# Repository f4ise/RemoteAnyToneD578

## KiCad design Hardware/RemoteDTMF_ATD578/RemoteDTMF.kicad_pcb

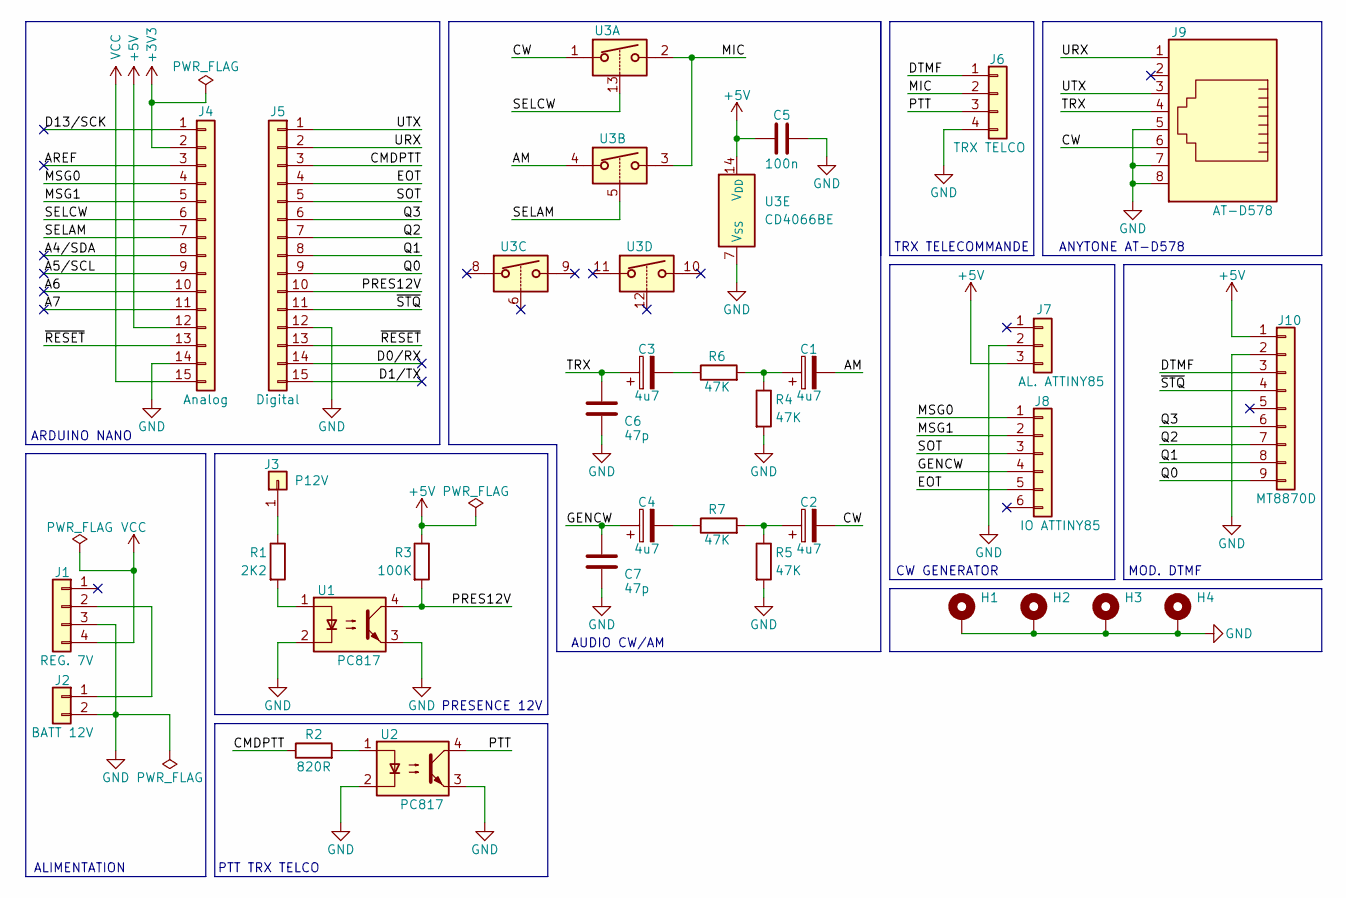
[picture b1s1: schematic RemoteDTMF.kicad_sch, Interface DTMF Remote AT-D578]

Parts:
C1, C2, C3, C4: 4u7; CP_Radial_D5.0mm_P2.50mm
C5: 100n; C_Rect_L7.0mm_W3.5mm_P5.00mm
C6, C7: 47p; C_Rect_L7.0mm_W3.5mm_P5.00mm
H1, H2, H3, H4: MountingHole_Pad; MountingHole_3.2mm_M3_DIN965_Pad
J1: REG. 7V; PinHeader_1x04_P2.54mm_Vertical
J2: BATT 12V; TerminalBlock_MaiXu_MX126-5.0-02P_1x02_P5.00mm
J3: P12V; PinHeader_1x01_P2.54mm_Vertical
J4: Analog; PinHeader_1x15_P2.54mm_Vertical
J5: Digital; PinHeader_1x15_P2.54mm_Vertical
J6: TRX TELCO; PinHeader_1x04_P2.54mm_Vertical
J7: AL. ATTINY85; PinHeader_1x03_P2.54mm_Vertical
J8: IO ATTINY85; PinHeader_1x06_P2.54mm_Vertical
J9: AT-D578; RJ45_Amphenol_54602-x08_Horizontal
J10: MT8870D; PinHeader_1x09_P2.54mm_Vertical
R1: 2K2; R_Axial_DIN0204_L3.6mm_D1.6mm_P7.62mm_Horizontal
R2: 820R; R_Axial_DIN0204_L3.6mm_D1.6mm_P7.62mm_Horizontal
R3: 100K; R_Axial_DIN0204_L3.6mm_D1.6mm_P7.62mm_Horizontal
R4, R5, R6, R7: 47K; R_Axial_DIN0204_L3.6mm_D1.6mm_P7.62mm_Horizontal
U1, U2: PC817; DIP-4_W7.62mm
U3: CD4066BE; DIP-14_W7.62mm

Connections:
+3V3: J4.2
+5V: C5.1, J4.12, J7.3, J10.1, R3.1, U3.14 (V_{DD})
/A4/SDA: J4.8
/A5/SCL: J4.9
/A6: J4.10
/A7: J4.11
/AM: C1.2, U3.4
/AREF: J4.3
/CMDPTT: J5.3, R2.1
/CW: C2.2, J9.6, U3.1
/D0/RX: J5.14
/D1/TX: J5.15
/D13/SCK: J4.1
/DTMF: J6.1, J10.3
/EOT: J5.4, J8.5
/GENCW: C4.1, C7.1, J8.4
/MIC: J6.2, U3.2, U3.3
/MSG0: J4.4, J8.1
/MSG1: J4.5, J8.2
/PRES12V: J5.10, R3.2, U1.4
/PTT: J6.3, U2.4
/Q0: J5.9, J10.9
/Q1: J5.8, J10.8
/Q2: J5.7, J10.7
/Q3: J5.6, J10.6
/SELAM: J4.7, U3.5
/SELCW: J4.6, U3.13
/SOT: J5.5, J8.3
/TRX: C3.1, C6.1, J9.4
/URX: J5.2, J9.1
/UTX: J5.1, J9.3
/~RESET: J4.13, J5.13
/~STQ: J5.11, J10.4
GND: C5.2, C6.2, C7.2, H1.1, H2.1, H3.1, H4.1, J1.3, J2.2, J4.14, J5.12, J6.4, J7.2, J9.5, J9.7, J9.8, J10.2, R4.2, R5.2, U1.2, U1.3, U2.2, U2.3, U3.7 (V_{SS})
unnamed: C1.1, R4.1, R6.2
unnamed: C2.1, R5.1, R7.2
unnamed: C3.2, R6.1
unnamed: C4.2, R7.1
unnamed: J1.2, J2.1
unnamed: J3.1, R1.1
unnamed: R1.2, U1.1
unnamed: R2.2, U2.1
VCC: J1.4, J4.15

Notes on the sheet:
ALIMENTATION
ARDUINO NANO
AUDIO CW/AM
ANYTONE AT-D578
TRX TELECOMMANDE
MOD. DTMF
PRESENCE 12V
PTT TRX TELCO
CW GENERATOR

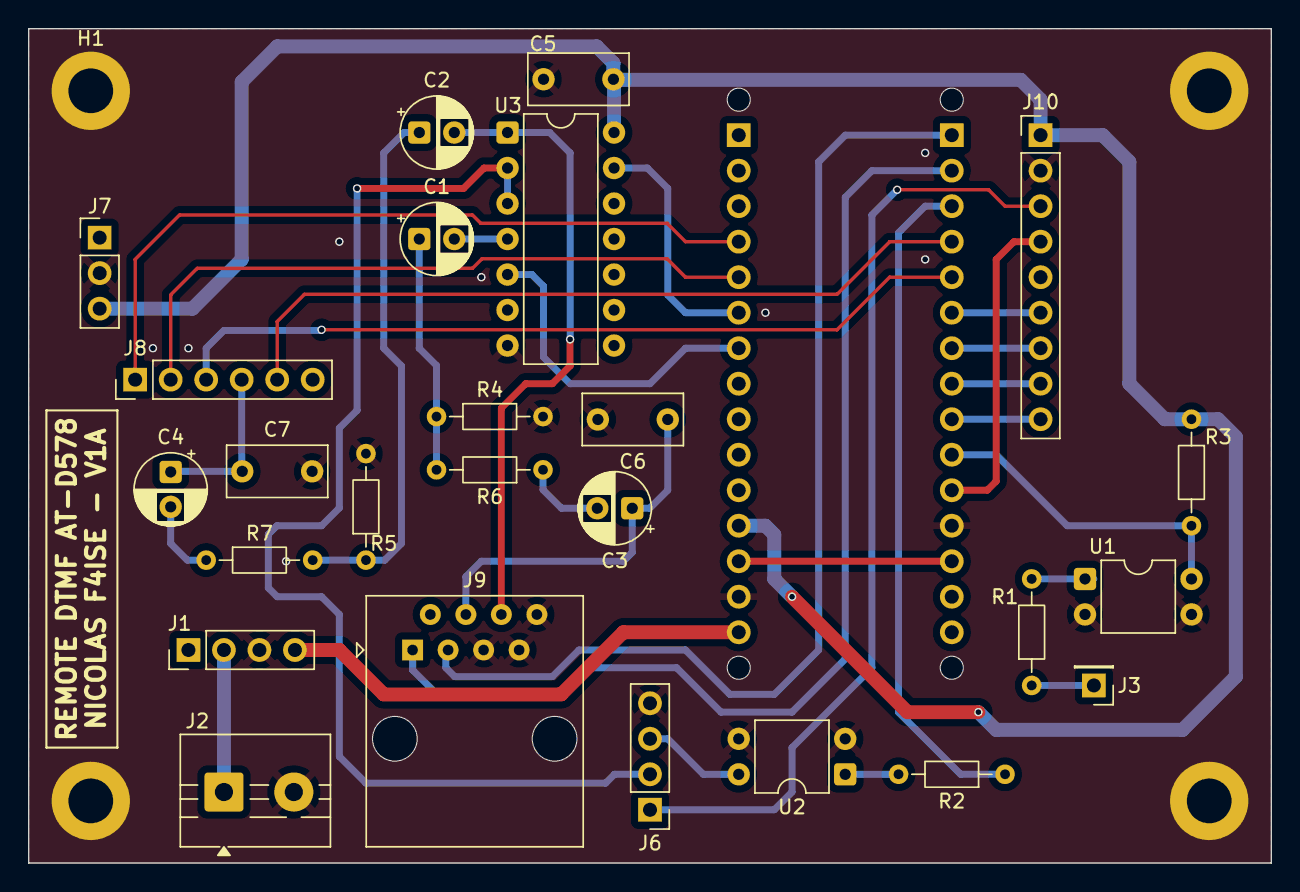
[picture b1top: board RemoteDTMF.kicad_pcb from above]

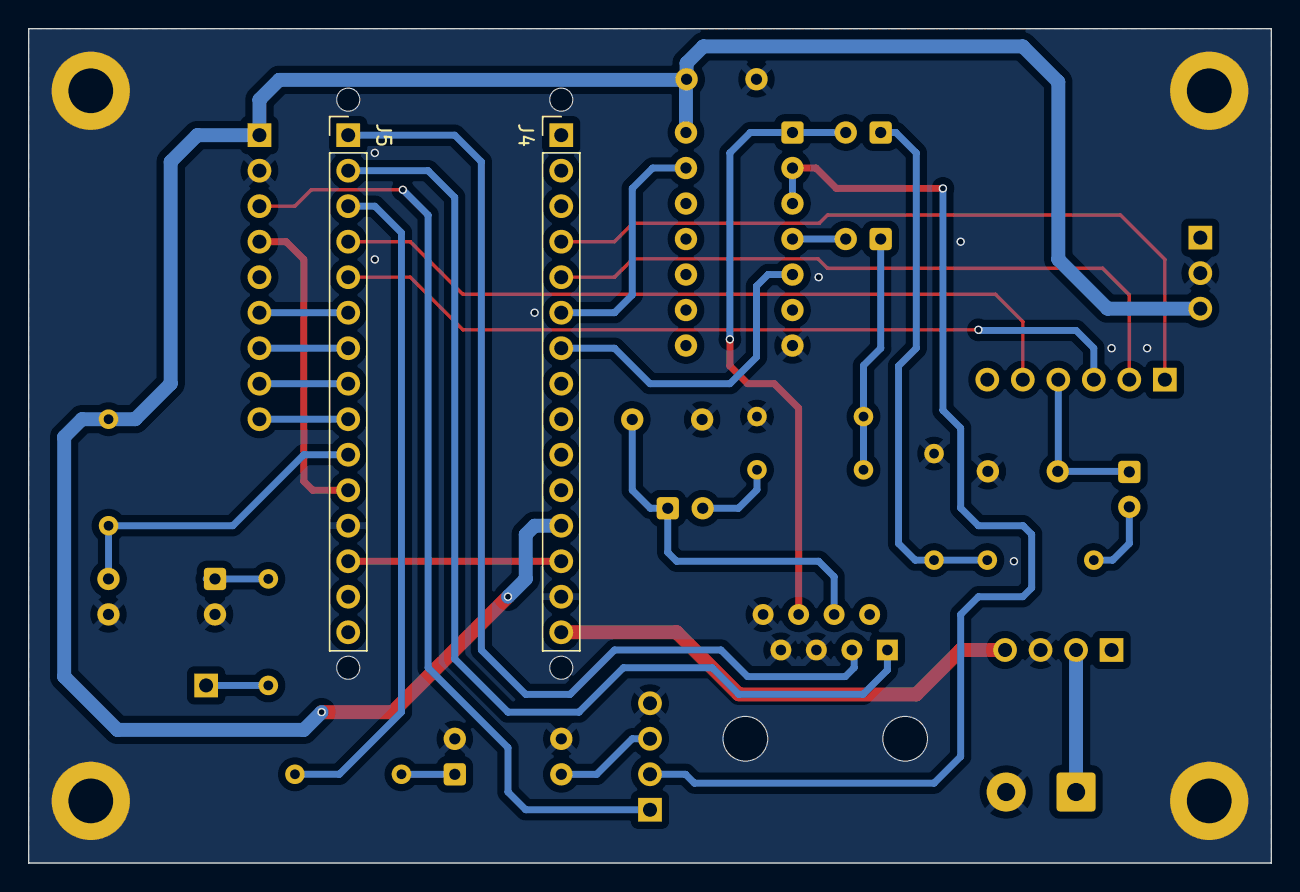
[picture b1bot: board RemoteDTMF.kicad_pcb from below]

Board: 2 copper layers, 88.9 x 59.7 mm, 35 parts (2 on the bottom side), 34 nets.

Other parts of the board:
MH1, MH2, MH3, MH4: MountingHole_65mil

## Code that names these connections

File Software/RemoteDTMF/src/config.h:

#ifndef CONFIG_H
#define CONFIG_H

#define VERSION     "0.9A"

#define LED         LED_BUILTIN

#define dbgSpeed    115200

// UART D578
#define swTX        11
#define swRX        12
#define swSPEED     115200 

// MT8870
#define STQ         2
#define Q0          4
#define Q1          5
#define Q2          6
#define Q3          7
#define timeOutDTMF 10      // Timeout DTMF

// DS3231
#define intRTC      3

// BEACON
#define MSG0_CW     14
#define MSG1_CW     15
#define SOT_CW      8
#define EOT_CW      9

// AUDIO AM
#define DURATION_AM 15      // Send Audio AM X sec.

// OPTO
#define PRES12V1     3      // TBD IO
#define PRES12V2     3      // TBD IO
#define CMDPTT      10

// SWITCH ANA
#define SW_CW       16
#define SW_AM       17

// Logs
#define INF   0
#define WAR   1
#define ERR   2

#endif

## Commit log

2025-09-06 Proof Of Concept
2025-09-06 Update Proof Of Concept
2025-09-07 Manage Press short, Press Long for A, B, C and D touch
2025-09-09 Work In Progress: Add morse beacon
2025-09-12 Update version 0.3A
    - Support Beacon CW
    - Refactoring code main
2025-09-15 Add Beacon CW
2025-09-25 Update Code, Add schematic, Add Docs
2025-09-25 Update schematic, add PCB and Gerber
2025-09-26 Comment Schematic, add PDF
2025-09-26 Update Gerber
2025-09-30 Update to 0.5A
    - Add terminal
    - Add EEPROM
    - add RTC Clock DS3231
2025-09-30 WIP 0.6A & Schematic
    - Support D578 microphone ACK
    - Update schematic
2025-10-04 WIP Update PCB
2025-10-05 WIP Update PCB 2
2025-10-05 WIP Update PCB 3
2025-10-07 WIP Update PCB 4
2025-10-07 Update 0.6A
    - Add relays
    - Add PIO
2025-10-08 Update to 0.7A
    - Change DTMF command
    - Bug fix ACK UART D578
2025-10-08 Update to 0.8A
    - Add Start / Stop mode
    - Add config date and time RTC
2025-10-18 Update 0.9A + Hardware Mega
    - Add EXT BME280
    - Update Doc
    - Add Schematic Remote_Mega
2025-10-30 Update projet
    - Clean Hardware folder
